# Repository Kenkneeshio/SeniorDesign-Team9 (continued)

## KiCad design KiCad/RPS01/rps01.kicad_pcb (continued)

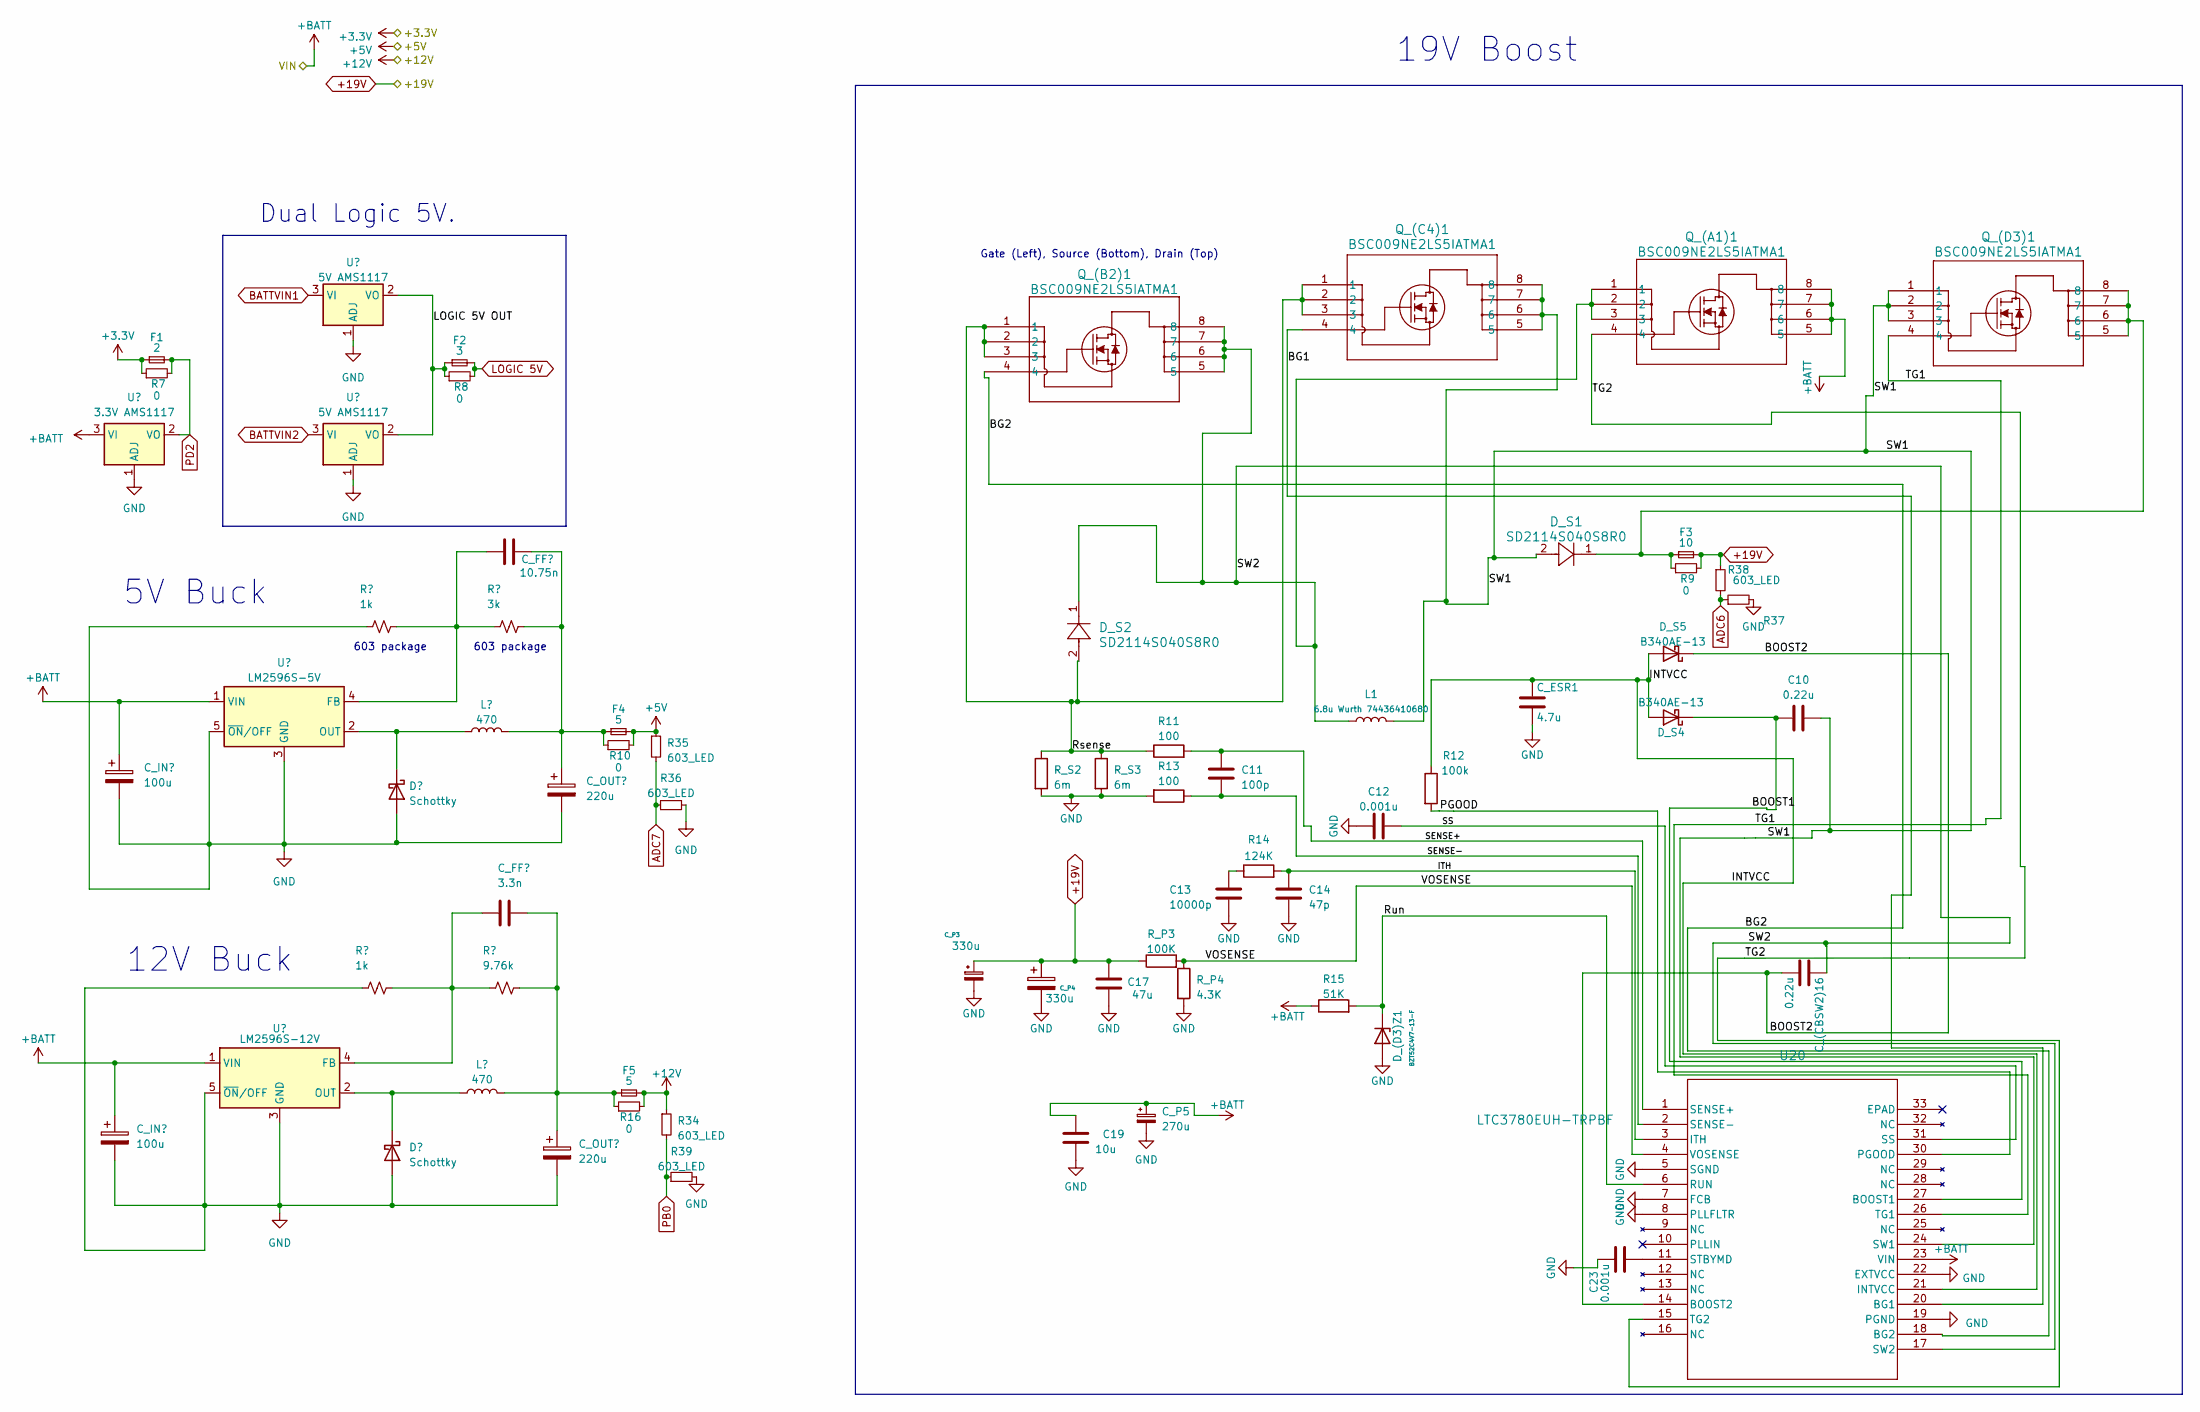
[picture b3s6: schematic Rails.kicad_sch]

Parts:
C9: 10.75n; C_0603_1608Metric
C10: 0.22u; C_1206_3216Metric
C11: 100p; C_1206_3216Metric
C12, C23: 0.001u; C_1206_3216Metric
C13: 10000p; C_1206_3216Metric
C14: 47p; C_1206_3216Metric
C15: 3.3n; C_0603_1608Metric
C17: 47u; C_1206_3216Metric
C19: 10u; C_1206_3216Metric
C_(CBSW2)16: 0.22u; C_1206_3216Metric
C_ESR1: 4.7u; LOWESRCAPMP7.6X4.3_3.1N_KEM
C_P1, C_P6: 100u; CP_Elec_8x10
C_P2, C_P7: 220u; CP_Elec_8x10
C_P3, C_P4: 330u; CAP_EEHZU1V331P
C_P5: 270u; LargeCAPSCAPPRD350W60D800H1200
D_(D3)Z1: BZT52C4V7-13-F; SOD123_DIO
D_S1, D_S2: SD2114S040S8R0; SD2114_AVX
D_S4, D_S5: B340AE-13; CR_SMA_320-340AE_DIO
D_S6, D_S8: Schottky; CR_SMA_320-340AE_DIO
F1: 2; 0154Series_LTF
F2: 3; 0154Series_LTF
F3: 10; 0154Series_LTF
F4, F5: 5; 0154Series_LTF
L1: 6.8u Wurth 74436410680; IND_410680_WRE
L2, L3: 470; IND_CDRH127&slash_LDNP-470MC_SUM
Q_(A1)1: BSC009NE2LS5IATMA1; PG-TDSON-8_INF
Q_(B2)1: BSC009NE2LS5IATMA1; PG-TDSON-8_INF
Q_(C4)1: BSC009NE2LS5IATMA1; PG-TDSON-8_INF
Q_(D3)1: BSC009NE2LS5IATMA1; PG-TDSON-8_INF
R7, R8, R9, R10, R16: 0; R_0603_1608Metric
R11, R13: 100; R_1206_3216Metric
R12: 100k; R_1206_3216Metric
R14: 124K; R_1206_3216Metric
R15: 51K; R_1206_3216Metric
R34, R35, R36, R37, R38, R39: 603_LED; R_0603_1608Metric
R_P1, R_P5: 1k; R_0603_1608Metric
R_P2: 3k; R_0603_1608Metric
R_P3: 100K; R_1206_3216Metric
R_P4: 4.3K; R_1206_3216Metric
R_P6: 9.76k; R_0603_1608Metric
R_S2, R_S3: 6m; R_2512_6332Metric
U11, U13: 5V AMS1117; SOT-223-3_TabPin2
U12: 3.3V AMS1117; SOT-223-3_TabPin2
U14: LM2596S-5V; TO-263-5_TabPin3
U16: LM2596S-12V; TO-263-5_TabPin3
U20: LTC3780EUH-TRPBF; QFN-32_UH_LIT

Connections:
+3.3V: F1.1, R7.1; also elsewhere on the board
+5V: F4.2, R10.2, R35.1; also elsewhere on the board
+12V: F5.2, R16.2, R34.1; also elsewhere on the board
+19V: C17.1, C_P3.1, C_P4.1, F3.2, R9.2, R37.1, R_P3.1; also elsewhere on the board
/Voltage Regulator Rails/BG1: Q_(C4)1.4, U20.20 (BG1)
/Voltage Regulator Rails/BG2: Q_(B2)1.4, U20.18 (BG2)
/Voltage Regulator Rails/BOOST1: C10.1, D_S4.1 (K), U20.27 (BOOST1)
/Voltage Regulator Rails/BOOST2: C_(CBSW2)16.2, D_S5.1 (K), U20.14 (BOOST2)
/Voltage Regulator Rails/INTVCC: C_ESR1.1, D_S4.2 (A), D_S5.2 (A), R12.1, U20.21 (INTVCC)
/Voltage Regulator Rails/ITH: C14.1, R14.2, U20.3 (ITH)
/Voltage Regulator Rails/LOGIC 5V OUT: F2.1, R8.1, U11.2 (VO), U13.2 (VO)
/Voltage Regulator Rails/PGOOD: R12.2, U20.30 (PGOOD)
/Voltage Regulator Rails/Rsense: D_S2.2, Q_(B2)1.1, Q_(B2)1.2, Q_(B2)1.3, Q_(C4)1.1, Q_(C4)1.2, Q_(C4)1.3, R11.1, R_S2.1, R_S3.1
/Voltage Regulator Rails/Run: D_(D3)Z1.1 (K), R15.2, U20.6 (RUN)
/Voltage Regulator Rails/SENSE+: C11.2, R11.2, U20.1 (SENSE+)
/Voltage Regulator Rails/SENSE-: C11.1, R13.1, U20.2 (SENSE-)
/Voltage Regulator Rails/SS: C12.2, U20.31 (SS)
/Voltage Regulator Rails/SW1: C10.2, D_S1.2, L1.2, Q_(C4)1.5, Q_(C4)1.6, Q_(C4)1.7, Q_(C4)1.8, Q_(D3)1.1, Q_(D3)1.2, Q_(D3)1.3, U20.24 (SW1)
/Voltage Regulator Rails/SW2: C_(CBSW2)16.1, D_S2.1, L1.1, Q_(A1)1.1, Q_(A1)1.2, Q_(A1)1.3, Q_(B2)1.5, Q_(B2)1.6, Q_(B2)1.7, Q_(B2)1.8, U20.17 (SW2)
/Voltage Regulator Rails/TG1: Q_(D3)1.4, U20.26 (TG1)
/Voltage Regulator Rails/TG2: Q_(A1)1.4, U20.15 (TG2)
/Voltage Regulator Rails/VOSENSE: R_P3.2, R_P4.1, U20.4 (VOSENSE)
ADC6: R37.2, R38.1; also elsewhere on the board
ADC7: R35.2, R36.1; also elsewhere on the board
BATTVIN1: U11.3 (VI); also elsewhere on the board
BATTVIN2: U13.3 (VI); also elsewhere on the board
unnamed: C9.2, C_P2.1, F4.1, L2.2, R10.1, R_P2.2
unnamed: C13.1, R14.1
unnamed: C15.2, C_P7.1, F5.1, L3.2, R16.1, R_P6.2
unnamed: D_S1.1, F3.1, Q_(D3)1.5, Q_(D3)1.6, Q_(D3)1.7, Q_(D3)1.8, R9.1
unnamed: D_S6.1 (K), L3.1, U16.2 (OUT)
unnamed: D_S8.1 (K), L2.1, U14.2 (OUT)
unnamed: C9.1, R_P1.2, R_P2.1, U14.4 (FB)
unnamed: C15.1, R_P5.2, R_P6.1, U16.4 (FB)
unnamed: C23.1, U20.11 (STBYMD)
PB0: R34.2, R39.1; also elsewhere on the board
PD2: F1.2, R7.2, U12.2 (VO); also elsewhere on the board

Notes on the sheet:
19V Boost
603 package
5V Buck
Gate (Left), Source (Bottom), Drain (Top)
Dual Logic 5V.
12V Buck

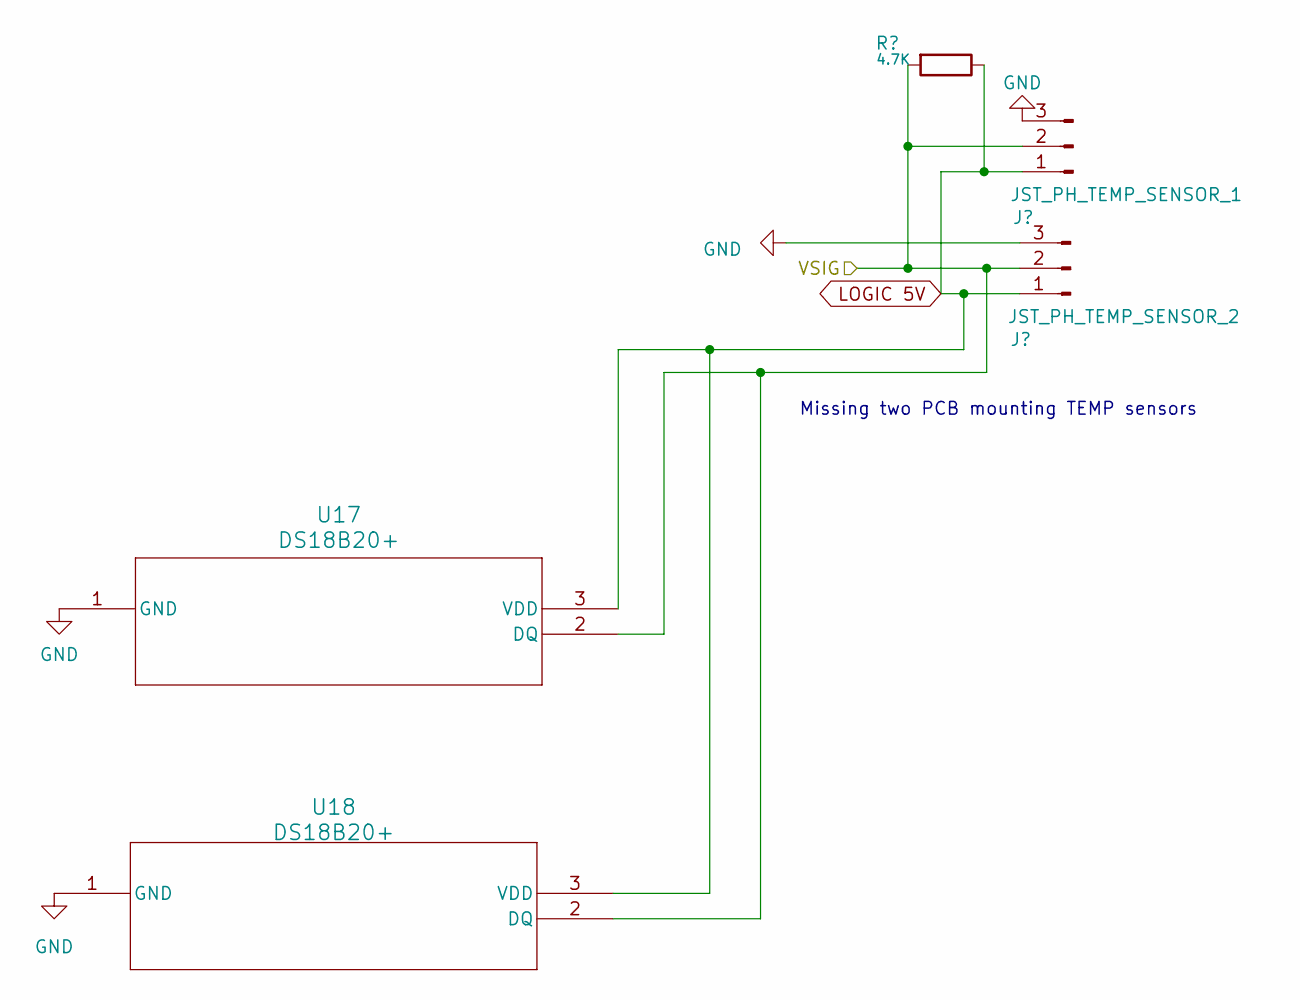
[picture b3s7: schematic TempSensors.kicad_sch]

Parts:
J13: JST_PH_TEMP_SENSOR_1; JST_PH_B3B-PH-K_1x03_P2.00mm_Vertical
J14: JST_PH_TEMP_SENSOR_2; JST_PH_B3B-PH-K_1x03_P2.00mm_Vertical
R27: 4.7K; R_0603_1608Metric
U17, U18: DS18B20+; TO-92L_Inline

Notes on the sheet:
Missing two PCB mounting TEMP sensors

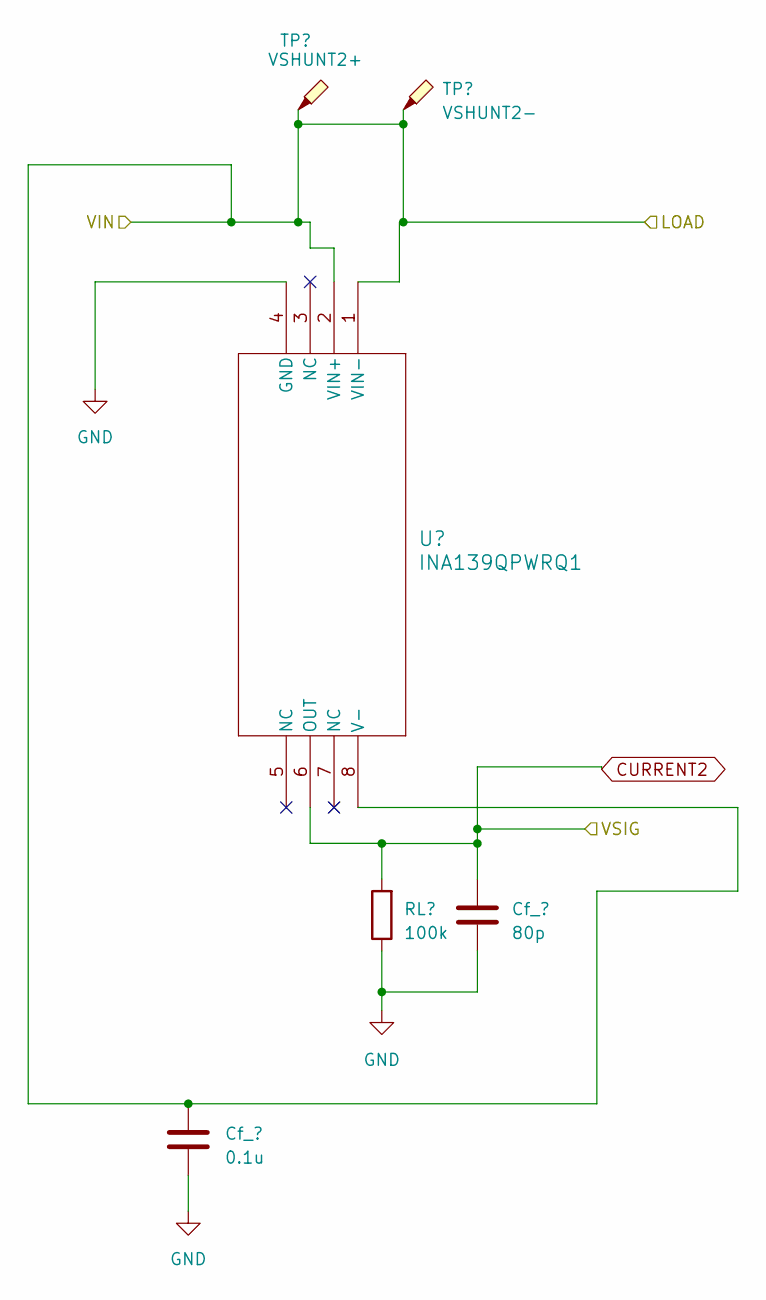
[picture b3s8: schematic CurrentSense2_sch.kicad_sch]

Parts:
C22: 80p; C_0603_1608Metric
Cf_1: 0.1u; C_0603_1608Metric
R31: 100k; R_0603_1608Metric
TP1: VSHUNT2-; CONN1_RCU-0C_TEC
TP2: VSHUNT2+; CONN1_RCU-0C_TEC
U19: INA139QPWRQ1; INA139_PW8

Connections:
CURRENT2: C22.1, R31.2, U19.6 (OUT); also elsewhere on the board

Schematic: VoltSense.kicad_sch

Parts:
C20, C21: 0.1u; C_0603_1608Metric
R_P7, R_P9: 1.2M; R_1206_3216Metric
R_P8, R_P10: 510K; R_1206_3216Metric

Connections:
BATTVIN1: R_P7.1; also elsewhere on the board
BATTVIN2: R_P9.1; also elsewhere on the board
VOLT1: C20.1, R_P7.2, R_P8.1; also elsewhere on the board
VOLT2: C21.1, R_P9.2, R_P10.1; also elsewhere on the board

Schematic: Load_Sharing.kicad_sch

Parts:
R1, R4: 100k; R_0603_1608Metric
R2, R3: 0; R_0603_1608Metric
U1, U2, U3, U5, U6, U7: NP100P04PLG-E1-AY; LTC3780_PRSS0004AL-A_REN
U4: LTC4416EMS-1-TRPBF; LTC4416_MSOP-10_MS_LIT

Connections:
/Load Sharing/E1: R1.2, R2.2, U4.2 (E1)
/Load Sharing/E2: R3.1, R4.1, U4.4 (*E2)
/Load Sharing/G1: U1.1 (GATE), U2.1 (GATE), U3.1 (GATE), U4.10 (G1)
/Load Sharing/G2: U4.6 (G2), U5.1 (GATE), U6.1 (GATE), U7.1 (GATE)
BATTVIN1: R2.1, U1.2 (DRAIN), U1.4 (FIN), U2.2 (DRAIN), U2.4 (FIN), U3.2 (DRAIN), U3.4 (FIN), U4.9 (V1); also elsewhere on the board
BATTVIN2: U4.7 (V2), U5.2 (DRAIN), U5.4 (FIN), U6.2 (DRAIN), U6.4 (FIN), U7.2 (DRAIN), U7.4 (FIN); also elsewhere on the board
PD6: R1.1; also elsewhere on the board
PD7: R4.2; also elsewhere on the board

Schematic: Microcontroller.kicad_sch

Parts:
C2, C3: 22p; C_0603_1608Metric
C4, C5, C6, C7: 0.1u; C_0603_1608Metric
C8: 100n; C_0603_1608Metric
J11: ISCP; PinHeader_2x03_P2.54mm_Vertical
J12: Serial; PinHeader_1x05_P2.54mm_Horizontal
R6: 0; R_0603_1608Metric
U9: ADR02AUJZ-REEL7; UJ_5_ADI
U10: ATmega328P-A; TQFP-32_7x7mm_P0.8mm
Y1: 16M; Crystal_SMD_HC49-SD

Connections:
/DPIN1: U10.1 (PD3); also elsewhere on the board
/DPIN13: U10.13 (PB1); also elsewhere on the board
/DPIN14: U10.14 (PB2); also elsewhere on the board
/Microcontroller/AVCC: C5.2, U10.18 (AVCC)
/Microcontroller/MISO: J11.1, U10.16 (PB4)
/Microcontroller/MOSI: J11.5, U10.15 (PB3)
/Microcontroller/PC4: U10.27 (PC4); also elsewhere on the board
/Microcontroller/PC5: U10.28 (PC5); also elsewhere on the board
/Microcontroller/RX: J12.3, U10.30 (PD0)
/Microcontroller/SCK: J11.2, U10.17 (PB5)
/Microcontroller/TX: J12.4, U10.31 (PD1)
/Microcontroller/VCC: C4.2, U10.4 (VCC), U10.6 (VCC)
/Microcontroller/XTAL1: C2.1, U10.7 (XTAL1/PB6), Y1.1
/Microcontroller/XTAL2: C3.1, U10.8 (XTAL2/PB7), Y1.2
ADC6: U10.19 (ADC6); also elsewhere on the board
ADC7: U10.22 (ADC7); also elsewhere on the board
AREF: C6.1, R6.1, U9.4 (VOUT); also elsewhere on the board
CURRENT1: U10.25 (PC2); also elsewhere on the board
CURRENT2: U10.26 (PC3); also elsewhere on the board
unnamed: C8.2, J12.5
unnamed: R6.2, U10.20 (AREF)
PB0: U10.12 (PB0); also elsewhere on the board
PD2: U10.32 (PD2); also elsewhere on the board
PD4: U10.2 (PD4); also elsewhere on the board
PD6: U10.10 (PD6); also elsewhere on the board
PD7: U10.11 (PD7); also elsewhere on the board
RST: C8.1, J11.3, U10.29 (~RESET/PC6); also elsewhere on the board
VOLT1: U10.23 (PC0); also elsewhere on the board
VOLT2: U10.24 (PC1); also elsewhere on the board

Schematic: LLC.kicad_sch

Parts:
Q1, Q2: BSS138; SOT-23
R17, R18, R22, R26: 0; R_0603_1608Metric
R19, R20, R23, R24: 10K; R_0603_1608Metric
R21, R25: 4.7K; R_0603_1608Metric

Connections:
+3.3V: Q1.1 (G), Q2.1 (G), R17.2, R19.1, R23.1; also elsewhere on the board
+5V: R18.1; also elsewhere on the board
/Logic Level Converter/IIC VOLT: R17.1, R18.2; also elsewhere on the board
/Microcontroller/PC4: Q1.3 (D), R20.2, R21.2, R22.2; also elsewhere on the board
/Microcontroller/PC5: Q2.3 (D), R24.2, R25.2, R26.2; also elsewhere on the board
SCL: Q2.2 (S), R23.2, R26.1; also elsewhere on the board
SDA: Q1.2 (S), R19.2, R22.1; also elsewhere on the board

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
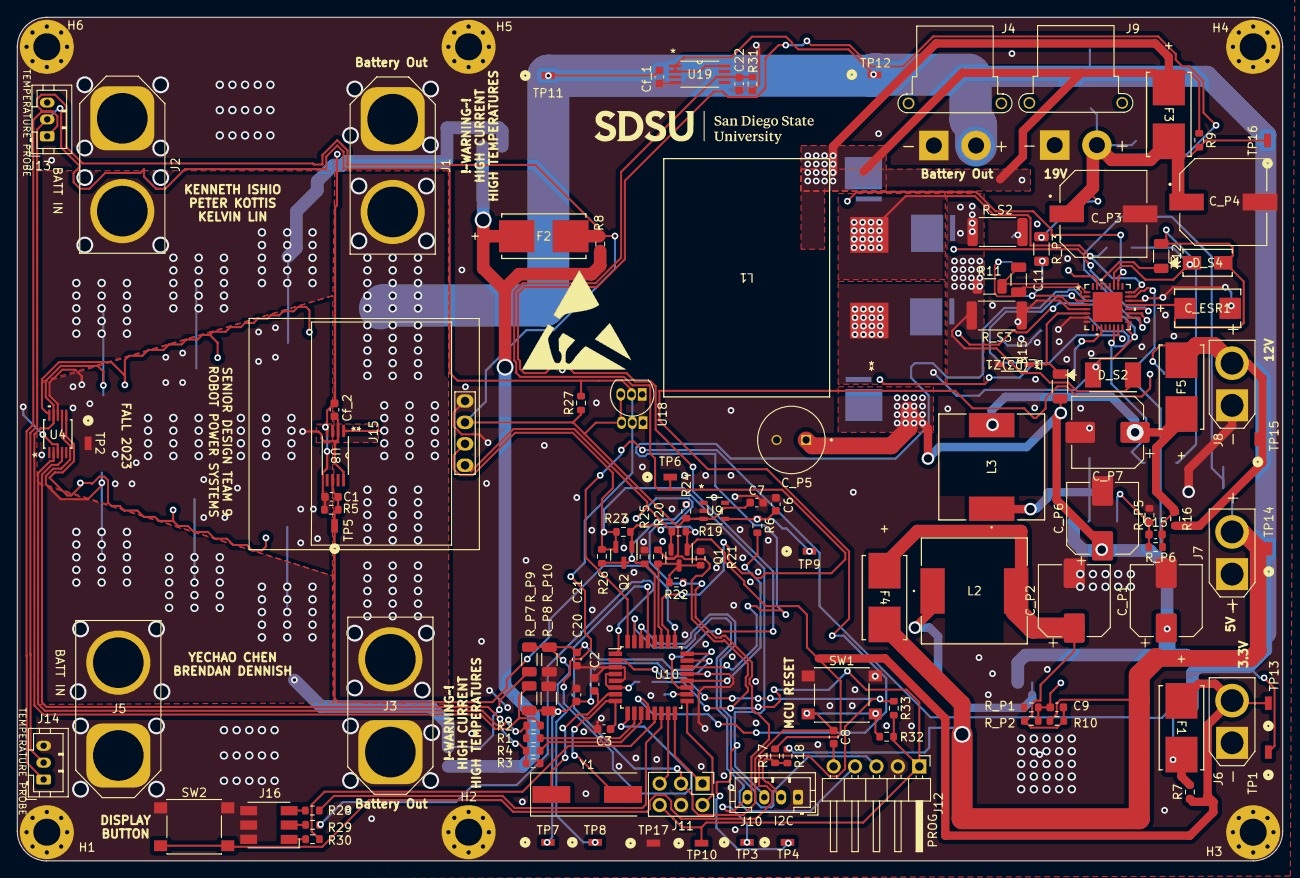
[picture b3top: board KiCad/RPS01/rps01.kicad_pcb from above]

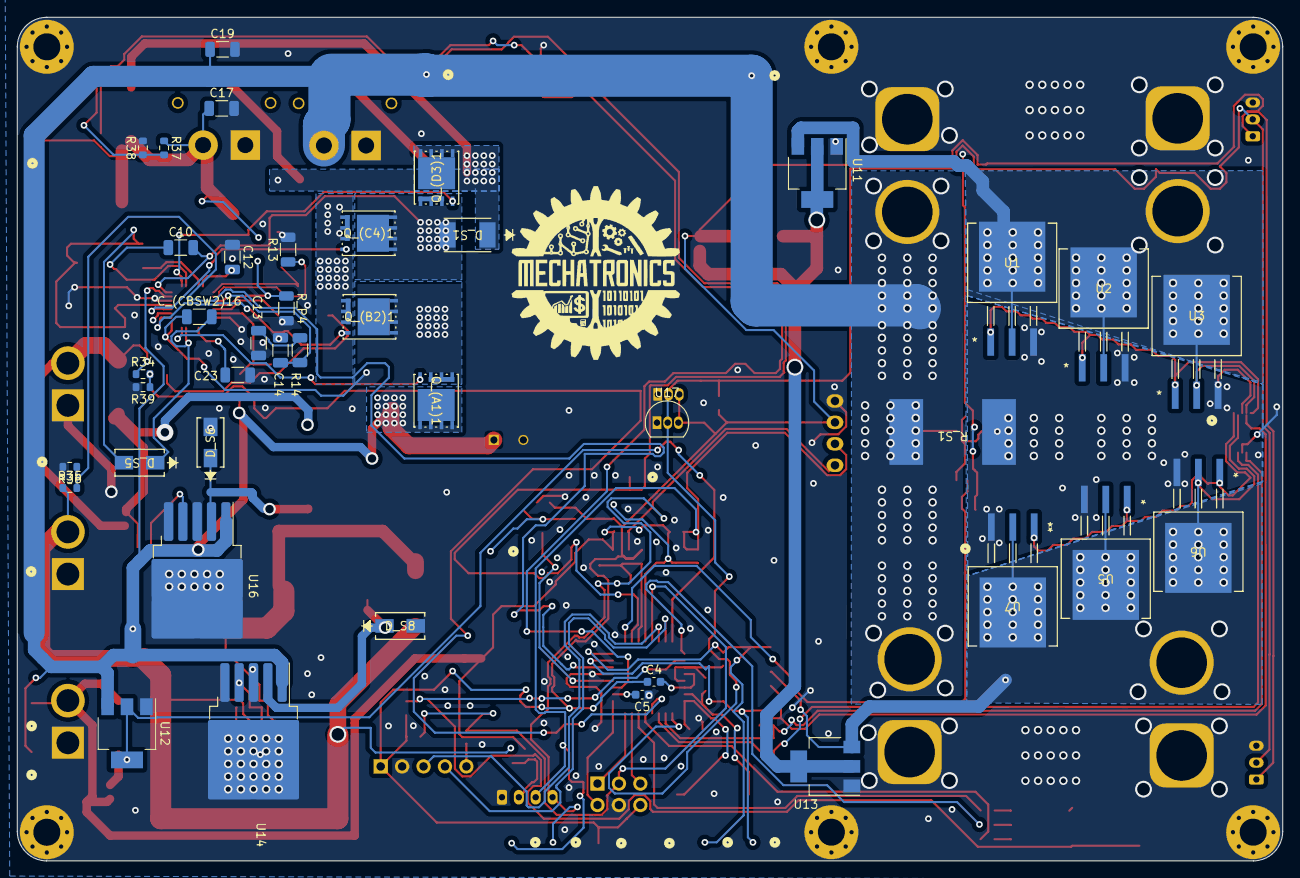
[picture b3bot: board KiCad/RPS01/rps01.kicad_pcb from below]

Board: 2 copper layers, 150.0 x 100.0 mm, 166 parts (40 on the bottom side), 77 nets.

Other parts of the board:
J16: RGB LED; LED_RGB_5050-6
R28: 150 Green; R_0603_1608Metric
TP11: VSHUNT2-; CONN1_RCU-0C_TEC
TP12: VSHUNT2+; CONN1_RCU-0C_TEC

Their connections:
/DPIN14: R28.2; also elsewhere on the board
unnamed: J16.3, R28.1

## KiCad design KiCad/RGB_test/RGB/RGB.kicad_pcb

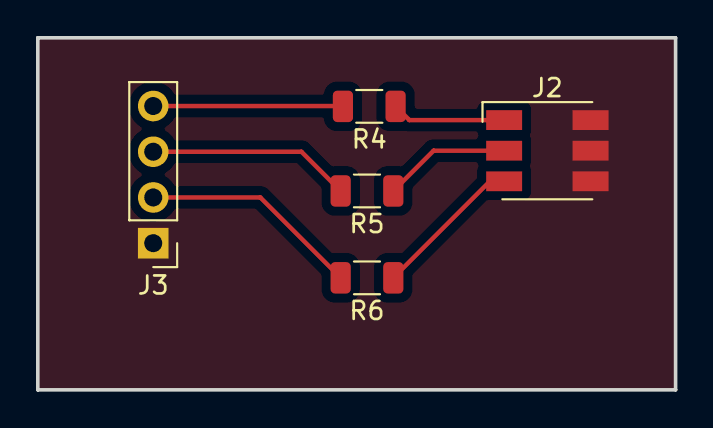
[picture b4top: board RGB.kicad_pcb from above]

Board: 2 copper layers, 35.4 x 19.6 mm, 5 parts (0 on the bottom side), 7 nets.

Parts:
J2: RGB LED; LED_RGB_5050-6
J3: Conn_01x04_Pin; PinHeader_1x04_P2.54mm_Vertical
R4: 150 Blue; R_1206_3216Metric
R5: 100 RED; R_1206_3216Metric
R6: 150 Green; R_1206_3216Metric

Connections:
GND: J2.4, J2.5, J2.6, J3.1
unnamed: J2.1, R4.1
unnamed: J2.2, R5.1
unnamed: J2.3, R6.1
unnamed: J3.2, R6.2
unnamed: J3.3, R5.2
unnamed: J3.4, R4.2

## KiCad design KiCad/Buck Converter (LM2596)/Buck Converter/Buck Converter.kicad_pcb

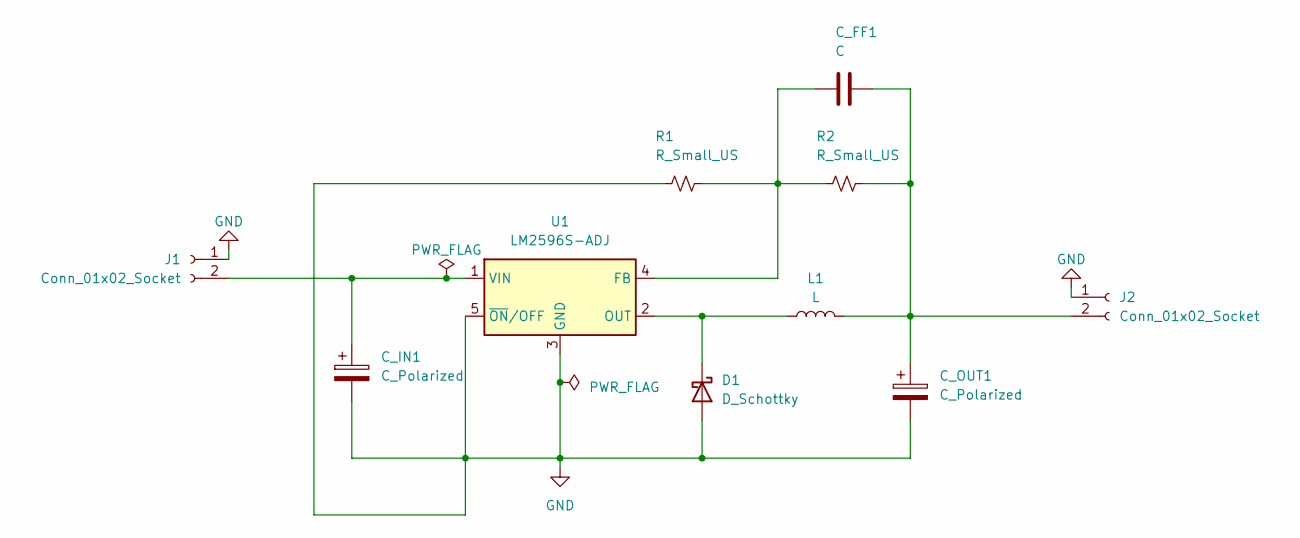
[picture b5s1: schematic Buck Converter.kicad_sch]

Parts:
C_FF1: C; C_1206_3216Metric
C_IN1: C_Polarized; CP_Elec_8x10
C_OUT1: C_Polarized; CP_Elec_8x10
D1: D_Schottky; CR_SMA_320-340AE_DIO
J1: Conn_01x02_Socket; AMASS_XT60-M_1x02_P7.20mm_Vertical
J2: Conn_01x02_Socket; AMASS_XT60-F_1x02_P7.20mm_Vertical
L1: L; IND_CDRH127_LDNP-470MC_SUM
R1, R2: R_Small_US; R_1206_3216Metric
U1: LM2596S-ADJ; TO-263-5_TabPin3

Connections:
GND: C_IN1.2, C_OUT1.2, D1.2 (A), J1.1, J2.1, R1.1, U1.3 (GND), U1.5 (~ON/OFF)
unnamed: D1.1 (K), L1.1, U1.2 (OUT)
unnamed: C_IN1.1, J1.2, U1.1 (VIN)
unnamed: C_FF1.2, C_OUT1.1, J2.2, L1.2, R2.2
unnamed: C_FF1.1, R1.2, R2.1, U1.4 (FB)

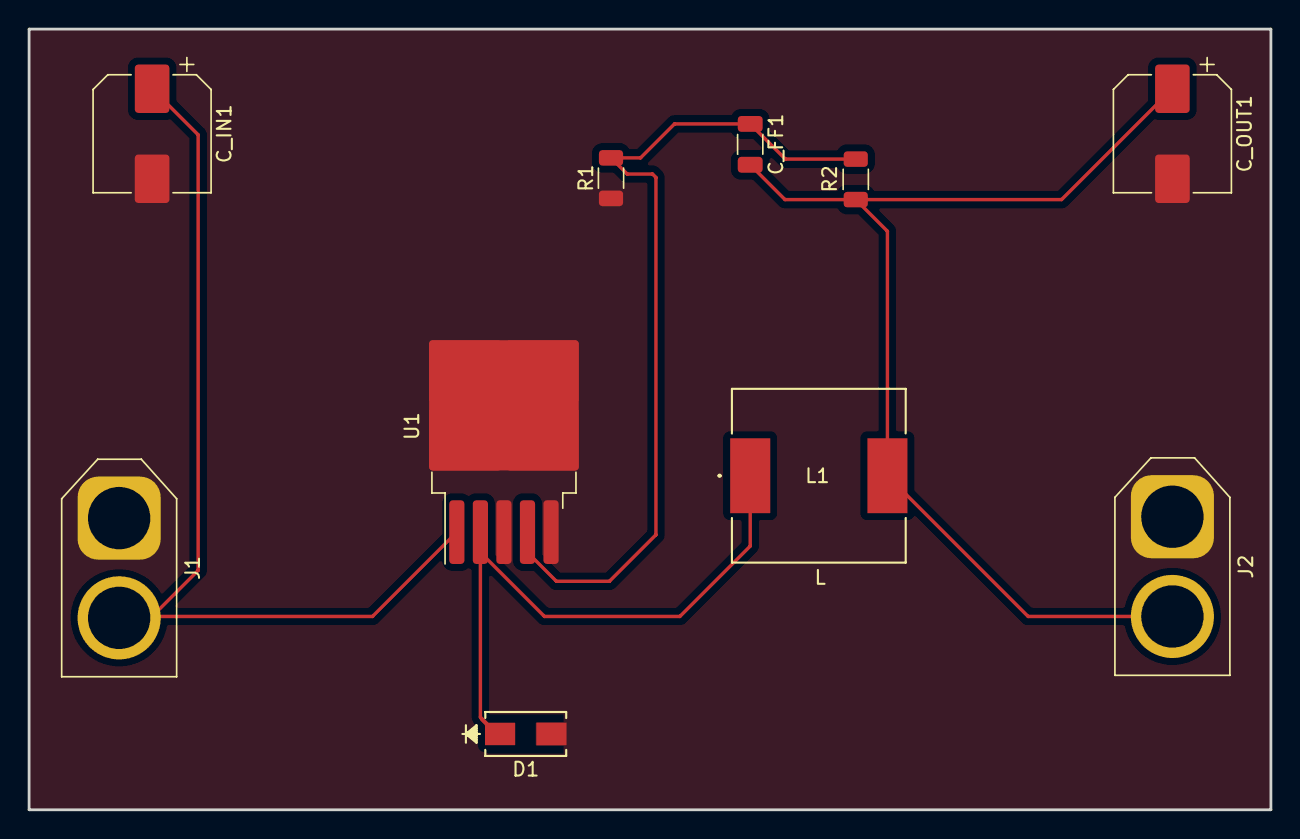
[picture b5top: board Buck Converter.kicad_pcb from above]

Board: 2 copper layers, 89.7 x 56.4 mm, 10 parts (0 on the bottom side), 5 nets.

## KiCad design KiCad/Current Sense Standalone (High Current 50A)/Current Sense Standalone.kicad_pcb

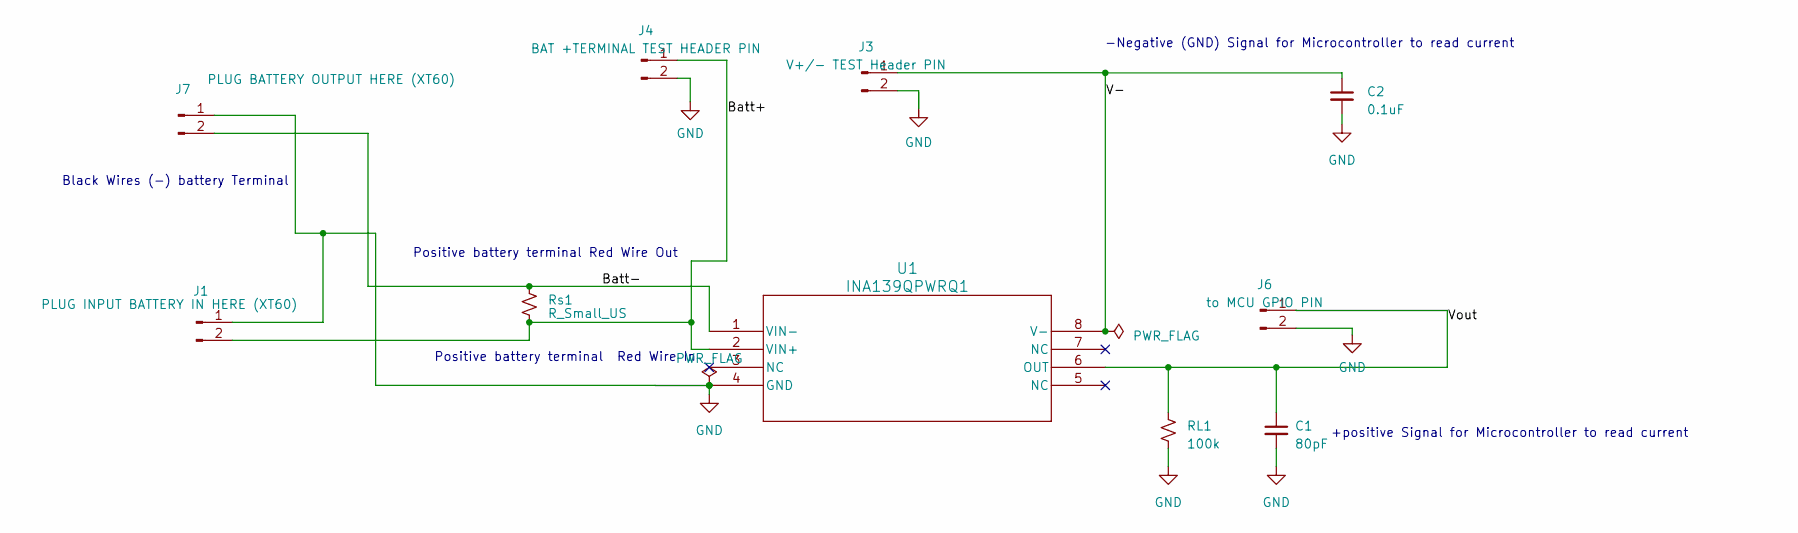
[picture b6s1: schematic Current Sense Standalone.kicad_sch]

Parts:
C1: 80pF; C_1206_3216Metric
C2: 0.1uF; C_1206_3216Metric
J1: PLUG INPUT BATTERY IN HERE (XT60); AMASS_XT60-M_1x02_P7.20mm_Vertical
J3: V+/- TEST Header PIN; PinHeader_1x02_P2.54mm_Vertical
J4: BAT +TERMINAL TEST HEADER PIN; PinHeader_1x02_P2.54mm_Vertical
J6: to MCU GPIO PIN; PinHeader_1x02_P2.54mm_Vertical
J7: PLUG BATTERY OUTPUT HERE (XT60); AMASS_XT60-F_1x02_P7.20mm_Vertical
RL1: 100k; RESC3216X65
Rs1: R_Small_US; Bourns-CSS2H-3920R-L300F-MFG
U1: INA139QPWRQ1; INA139_PW8

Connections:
/Batt+: J1.2, J4.1, Rs1.2, U1.2 (VIN+)
/Batt-: J7.2, Rs1.1, U1.1 (VIN-)
/V-: C2.1, J3.1, U1.8 (V-)
/Vout: C1.1, J6.1, RL1.1, U1.6 (OUT)
GND: C1.2, C2.2, J1.1, J3.2, J4.2, J6.2, J7.1, RL1.2, U1.4 (GND)

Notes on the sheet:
+positive Signal for Microcontroller to read current
-Negative (GND) Signal for Microcontroller to read current
Positive battery terminal Red Wire In
Black Wires (-) battery Terminal
Positive battery terminal Red Wire Out

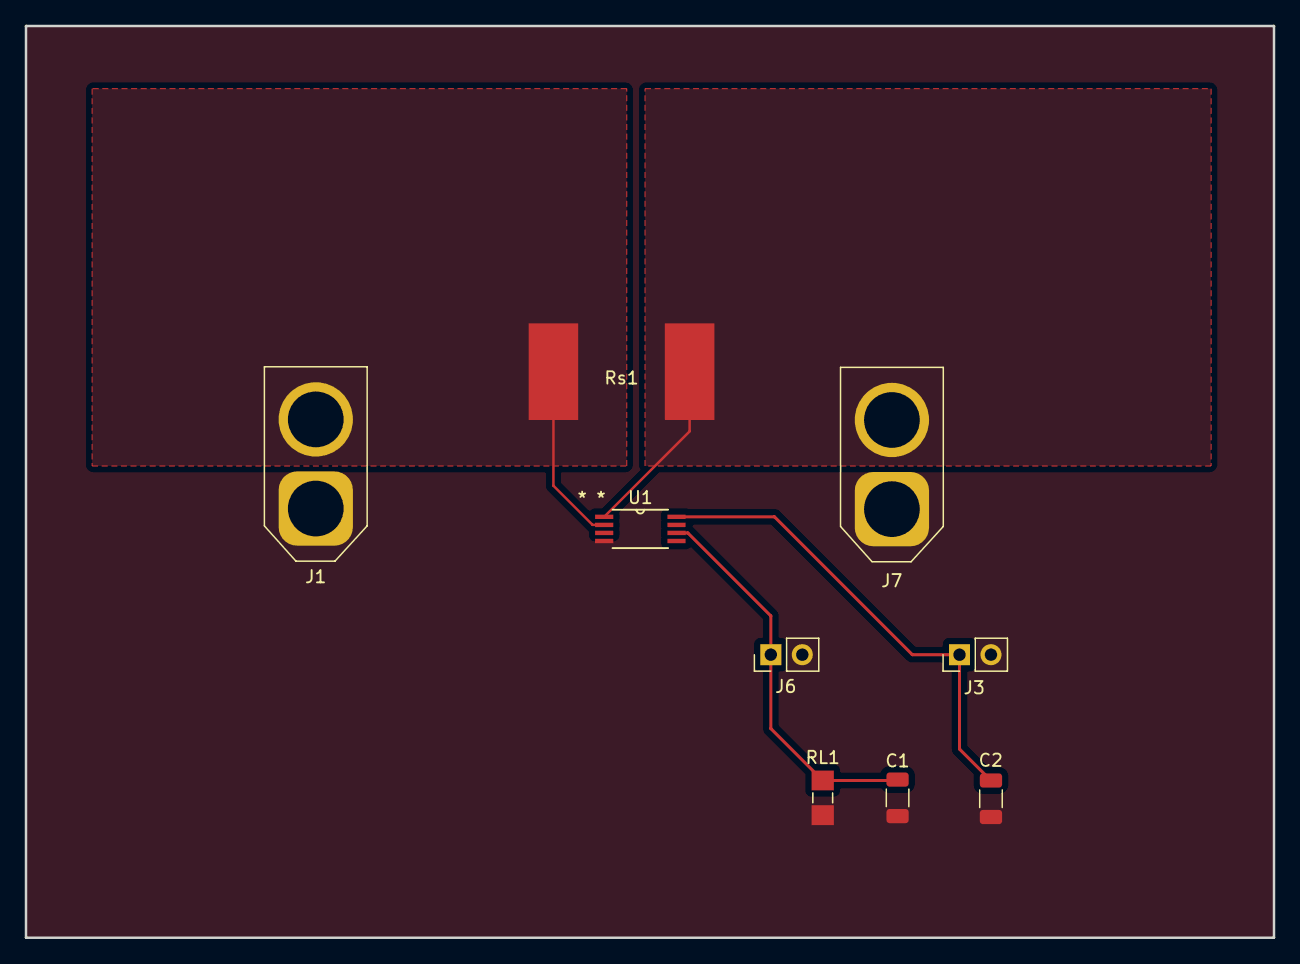
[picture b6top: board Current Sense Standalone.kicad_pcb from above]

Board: 2 copper layers, 100.8 x 73.6 mm, 9 parts (0 on the bottom side), 5 nets.

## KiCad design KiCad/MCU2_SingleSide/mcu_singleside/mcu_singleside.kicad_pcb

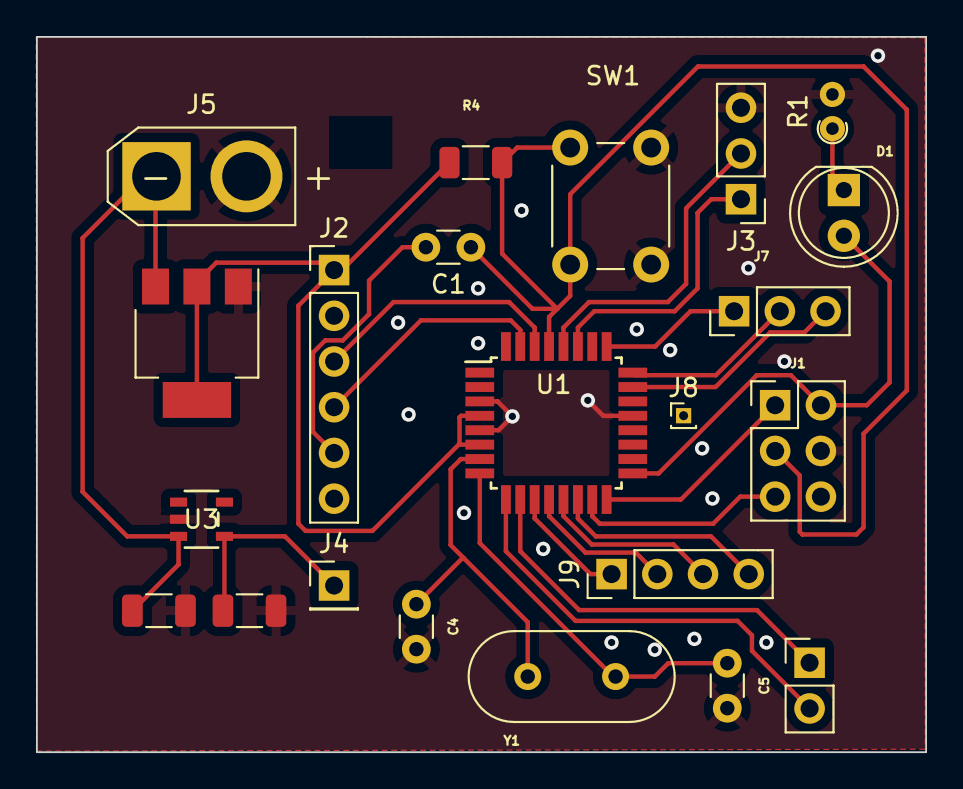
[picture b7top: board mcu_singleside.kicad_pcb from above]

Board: 2 copper layers, 49.4 x 39.7 mm, 22 parts (0 on the bottom side), 22 nets.

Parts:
C1: 100nF; C_Disc_D3.0mm_W1.6mm_P2.50mm
C2, C3: 0.1uf; C_1206_3216Metric
C4, C5: 0.22pf; C_Disc_D3.0mm_W1.6mm_P2.50mm
D1: MCU_LED; LED_D5.0mm
J1: Conn_02x03_Counter_Clockwise; PinHeader_2x03_P2.54mm_Vertical
J2: Conn_01x06; PinHeader_1x06_P2.54mm_Vertical
J3, J7: Conn_01x03; PinHeader_1x03_P2.54mm_Vertical
J4: Conn_01x02_Pin; PinHeader_1x01_P2.54mm_Vertical
J5: XT30; AMASS_XT30U-F_1x02_P5.0mm_Vertical
J6: AandDpin; PinHeader_1x02_P2.54mm_Vertical
J8: Conn_01x01_Pin; PinHeader_1x01_P1.00mm_Vertical
J9: Conn_01x04_Pin; PinHeader_1x04_P2.54mm_Vertical
R1: 1k; R_Axial_DIN0204_L3.6mm_D1.6mm_P1.90mm_Vertical
R4: 10K; R_1206_3216Metric
SW1: MCU_Button; SW_PUSH_6mm
U1: ATmega328P-A; TQFP-32_7x7mm_P0.8mm
U2: AMS1117; SOT-223-3_TabPin2
U3: ADR02AUJZ-REEL7; UJ_5_ADI
Y1: Crystal; Crystal_HC49-4H_Vertical

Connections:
+5V: J1.6, J2.1, R4.2, U1.4 (VCC), U1.6 (VCC), U2.2 (VO)
/AREF: J8.1, U1.20 (AREF)
/Analog: J6.1, U1.10 (PD6)
/Digital: J6.2, U1.9 (PD5)
/MISO: J1.1, U1.16 (PB4)
/MOSI: J1.5, U1.15 (PB3)
/RESET: C1.1, J1.3, R4.1, SW1.2 (B), U1.29 (~RESET/PC6)
/RST: C1.2, J2.5
/RX: J2.3, U1.30 (PD0)
/SCK: D1.2 (A), J1.2, U1.17 (PB5)
/SCL: J3.2, U1.28 (PC5)
/SDA: J3.1, U1.27 (PC4)
/TX: J2.4, U1.31 (PD1)
/VI: C2.1, J5.1, U2.3 (VI), U3.3 (VIN)
/VOUT: C3.1, J4.1, U3.4 (VOUT)
GND: C2.2, C3.2, C4.2, C5.2, J1.4, J2.2, J3.3, J5.2, R1.2, SW1.1 (A), U1.3 (GND), U1.5 (GND), U1.21 (GND), U2.1 (ADJ), U3.2 (GND)
unnamed: D1.1 (K), R1.1
unnamed: J7.1, U1.25 (PC2)
unnamed: J7.2, U1.24 (PC1)
unnamed: J7.3, U1.23 (PC0)
unnamed: C4.1, U1.7 (XTAL1/PB6), Y1.1
unnamed: C5.1, U1.8 (XTAL2/PB7), Y1.2
